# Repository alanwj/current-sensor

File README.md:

Current Sensor
---------
A current sensor.

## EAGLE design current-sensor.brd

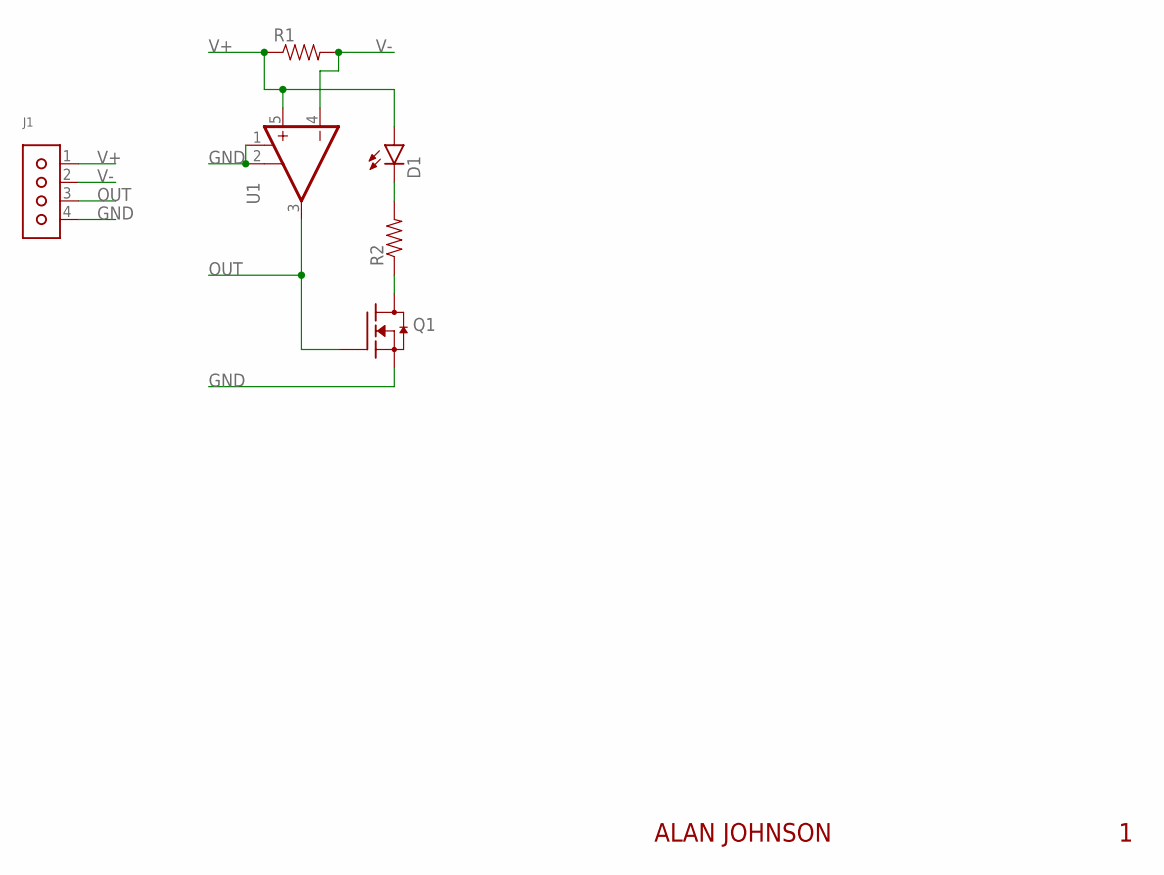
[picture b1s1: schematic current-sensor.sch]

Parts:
D1: LED1206; LED-1206
J1: 1X04
Q1: AO3416; SOT23-3
R1, R2: RESISTOR0805; 0805
U1: TS1102; SOT23-5

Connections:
GND: J1.4, Q1.2 (S), U1.1 (GND), U1.2 (GND)
unnamed: Q1.3 (D), R2.1
unnamed: D1.C, R2.2
OUT: J1.3, Q1.1 (G), U1.3 (OUT)
V+: D1.A, J1.1, R1.1, U1.5 (+IN)
V-: J1.2, R1.2, U1.4 (-IN)

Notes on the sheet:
ALAN JOHNSON

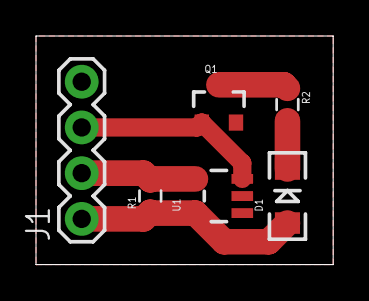
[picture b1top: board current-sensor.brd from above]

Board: 2 copper layers, 16.5 x 12.7 mm, 6 parts (0 on the bottom side), 6 nets.

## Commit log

2014-10-31 Add the first revision of a current sensor PCB.
2014-10-31 Add a CAM job.
2014-10-31 Add a .gitignore.
2014-10-31 Update CAM file to output to a subdirectory. Include CAM output.
2014-10-31 Add a minimal README.
2014-10-31 Add pin labels.
2014-11-01 Add identifying text "Current Sensor" to the bottom silk screen.
